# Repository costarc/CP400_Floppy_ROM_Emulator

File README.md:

# CP400_Floppy_ROM_Emulator
ROM and Floppy emulator for the CP 400 Color Computer, a TRS-80 Color clone made in Brasil.

This is a working in progress - the PCBs are not yet verified, and I cannot confirm they are functional.

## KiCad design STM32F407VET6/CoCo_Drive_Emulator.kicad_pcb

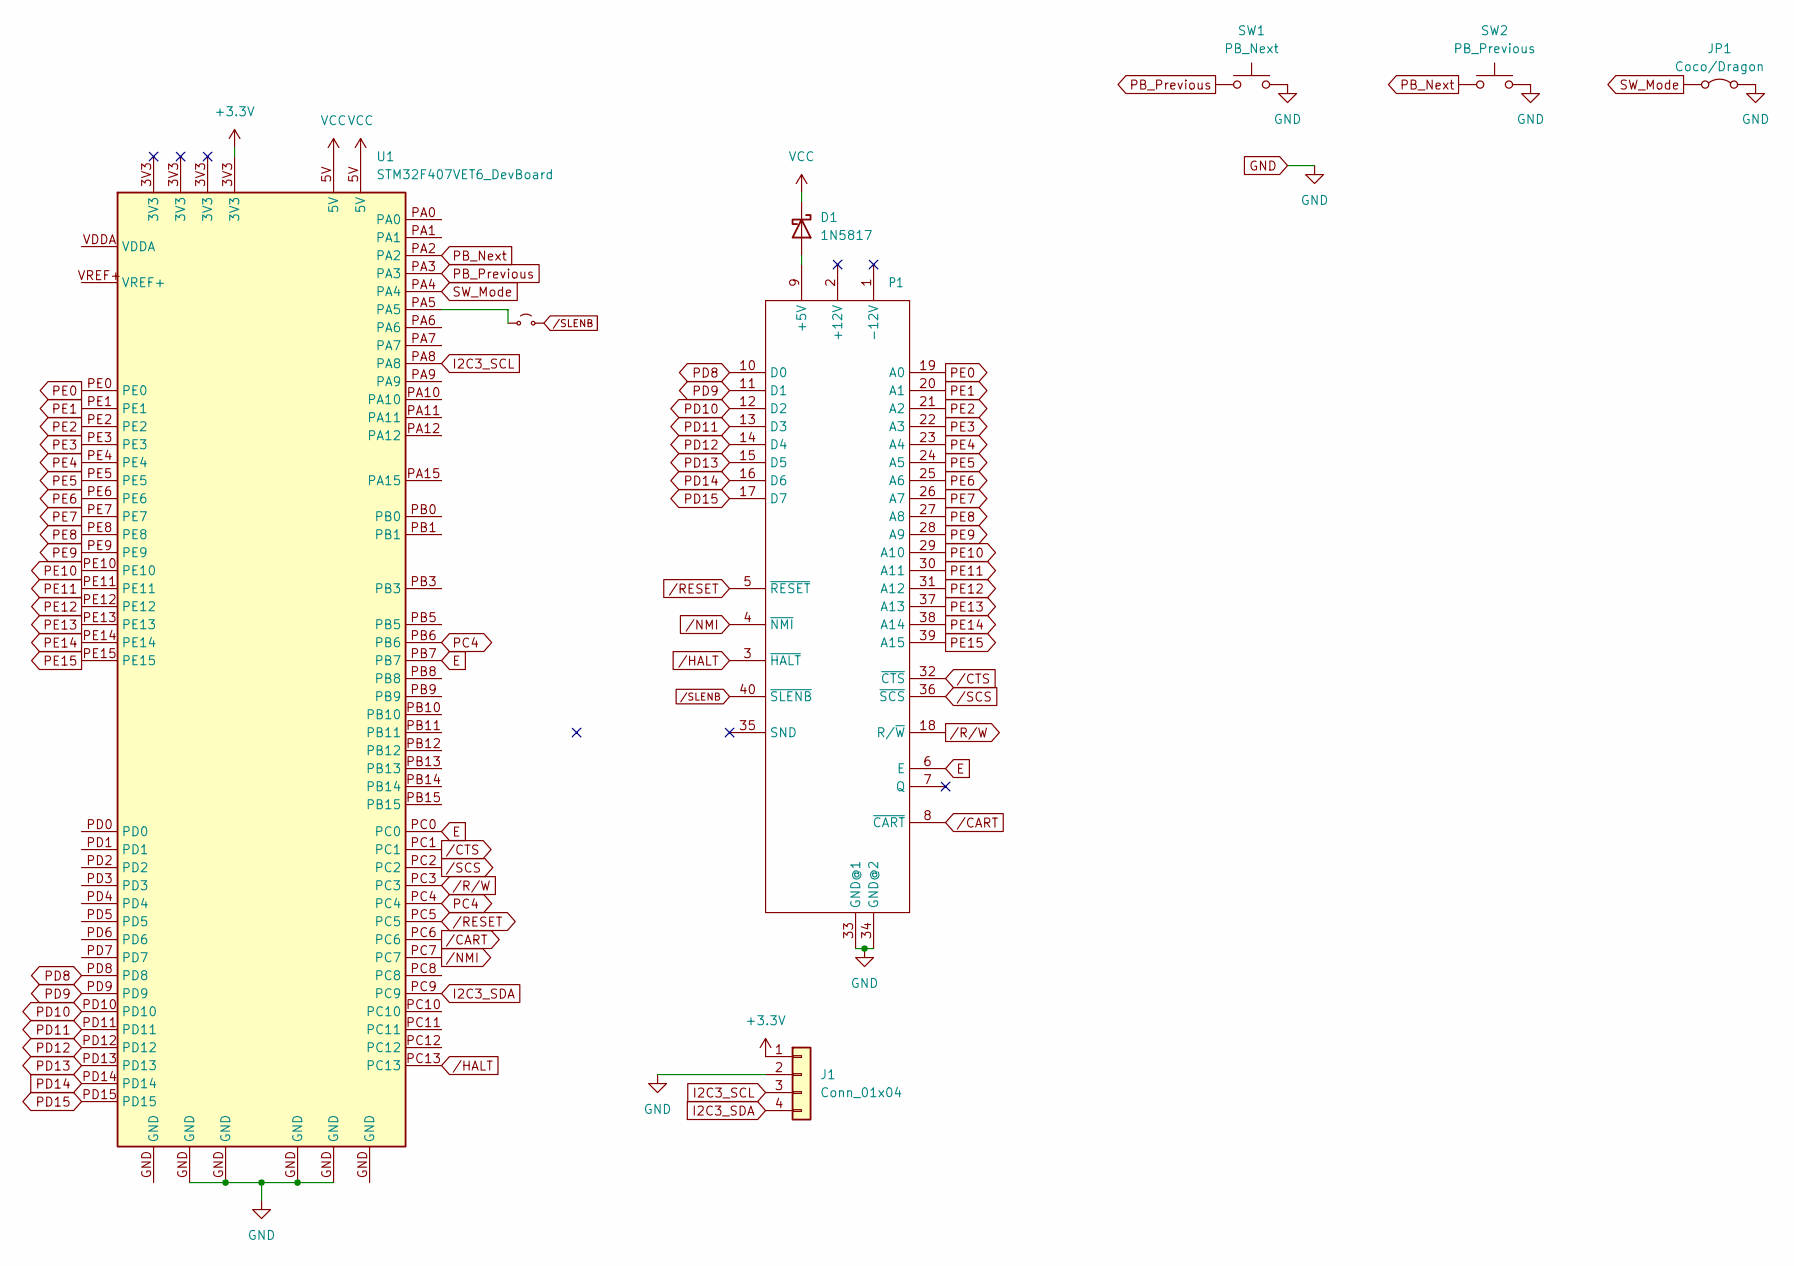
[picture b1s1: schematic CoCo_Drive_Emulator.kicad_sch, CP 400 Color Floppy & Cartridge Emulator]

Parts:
D1: 1N5817; Diode THT 30mm
J1: Conn_01x04; PinSocket_1x04_P2.54mm_Vertical
JP1: Coco/Dragon; PinHeader_1x02_P2.54mm_Horizontal
JP2: /SLENB; SolderJumper-2_P1.3mm_Open_Pad1.0x1.5mm
P1: CoCo_Slot; CP400-CART-LONG_v1
SW1: PB_Next; SW_PUSH_6mm_2Holes
SW2: PB_Previous; SW_PUSH_6mm_2Holes
U1: STM32F407VET6_DevBoard

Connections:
+3.3V: J1.1, U1.3V3
E: P1.6 (E), U1.PB7, U1.PC0
GND: J1.2, JP1.2 (B), P1.33 (GND@1), P1.34 (GND@2), SW1.2, SW2.2, U1.GND
I2C3_SCL: J1.3, U1.PA8
I2C3_SDA: J1.4, U1.PC9
unnamed: D1.2 (A), P1.9 (+5V)
unnamed: JP2.1 (A), U1.PA5
PB_Next: SW2.1, U1.PA2
PB_Previous: SW1.1, U1.PA3
PC4: U1.PB6, U1.PC4
PD8: P1.10 (D0), U1.PD8
PD9: P1.11 (D1), U1.PD9
PD10: P1.12 (D2), U1.PD10
PD11: P1.13 (D3), U1.PD11
PD12: P1.14 (D4), U1.PD12
PD13: P1.15 (D5), U1.PD13
PD14: P1.16 (D6), U1.PD14
PD15: P1.17 (D7), U1.PD15
PE0: P1.19 (A0), U1.PE0
PE1: P1.20 (A1), U1.PE1
PE2: P1.21 (A2), U1.PE2
PE3: P1.22 (A3), U1.PE3
PE4: P1.23 (A4), U1.PE4
PE5: P1.24 (A5), U1.PE5
PE6: P1.25 (A6), U1.PE6
PE7: P1.26 (A7), U1.PE7
PE8: P1.27 (A8), U1.PE8
PE9: P1.28 (A9), U1.PE9
PE10: P1.29 (A10), U1.PE10
PE11: P1.30 (A11), U1.PE11
PE12: P1.31 (A12), U1.PE12
PE13: P1.37 (A13), U1.PE13
PE14: P1.38 (A14), U1.PE14
PE15: P1.39 (A15), U1.PE15
SW_Mode: JP1.1 (A), U1.PA4
VCC: D1.1 (K), U1.5V
/CART: P1.8 (~CART), U1.PC6
/CTS: P1.32 (~CTS), U1.PC1
/HALT: P1.3 (~HALT), U1.PC13
/NMI: P1.4 (~NMI), U1.PC7
/RESET: P1.5 (~RESET), U1.PC5
/R/W: P1.18 (R/~W), U1.PC3
/SCS: P1.36 (~SCS), U1.PC2
/SLENB: JP2.2 (B), P1.40 (~SLENB)

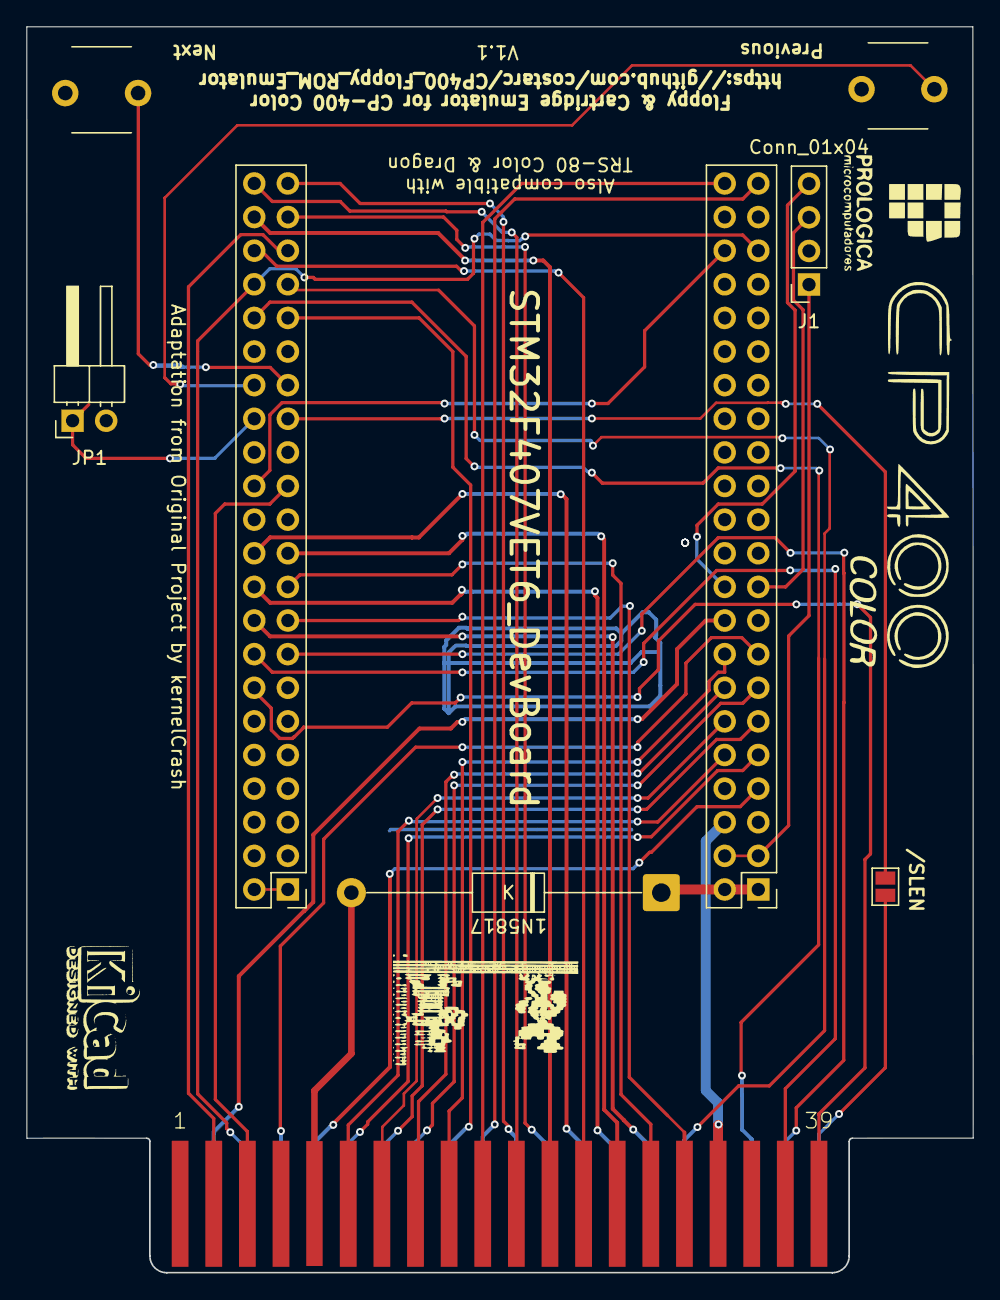
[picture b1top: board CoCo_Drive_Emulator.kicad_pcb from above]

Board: 2 copper layers, 71.4 x 94.1 mm, 8 parts (0 on the bottom side), 44 nets.

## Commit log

2025-10-05 Initial commit; v1.0 of both designs: STM32F407VET6 / STM32F407VGT6
2025-10-07 Added header for display
